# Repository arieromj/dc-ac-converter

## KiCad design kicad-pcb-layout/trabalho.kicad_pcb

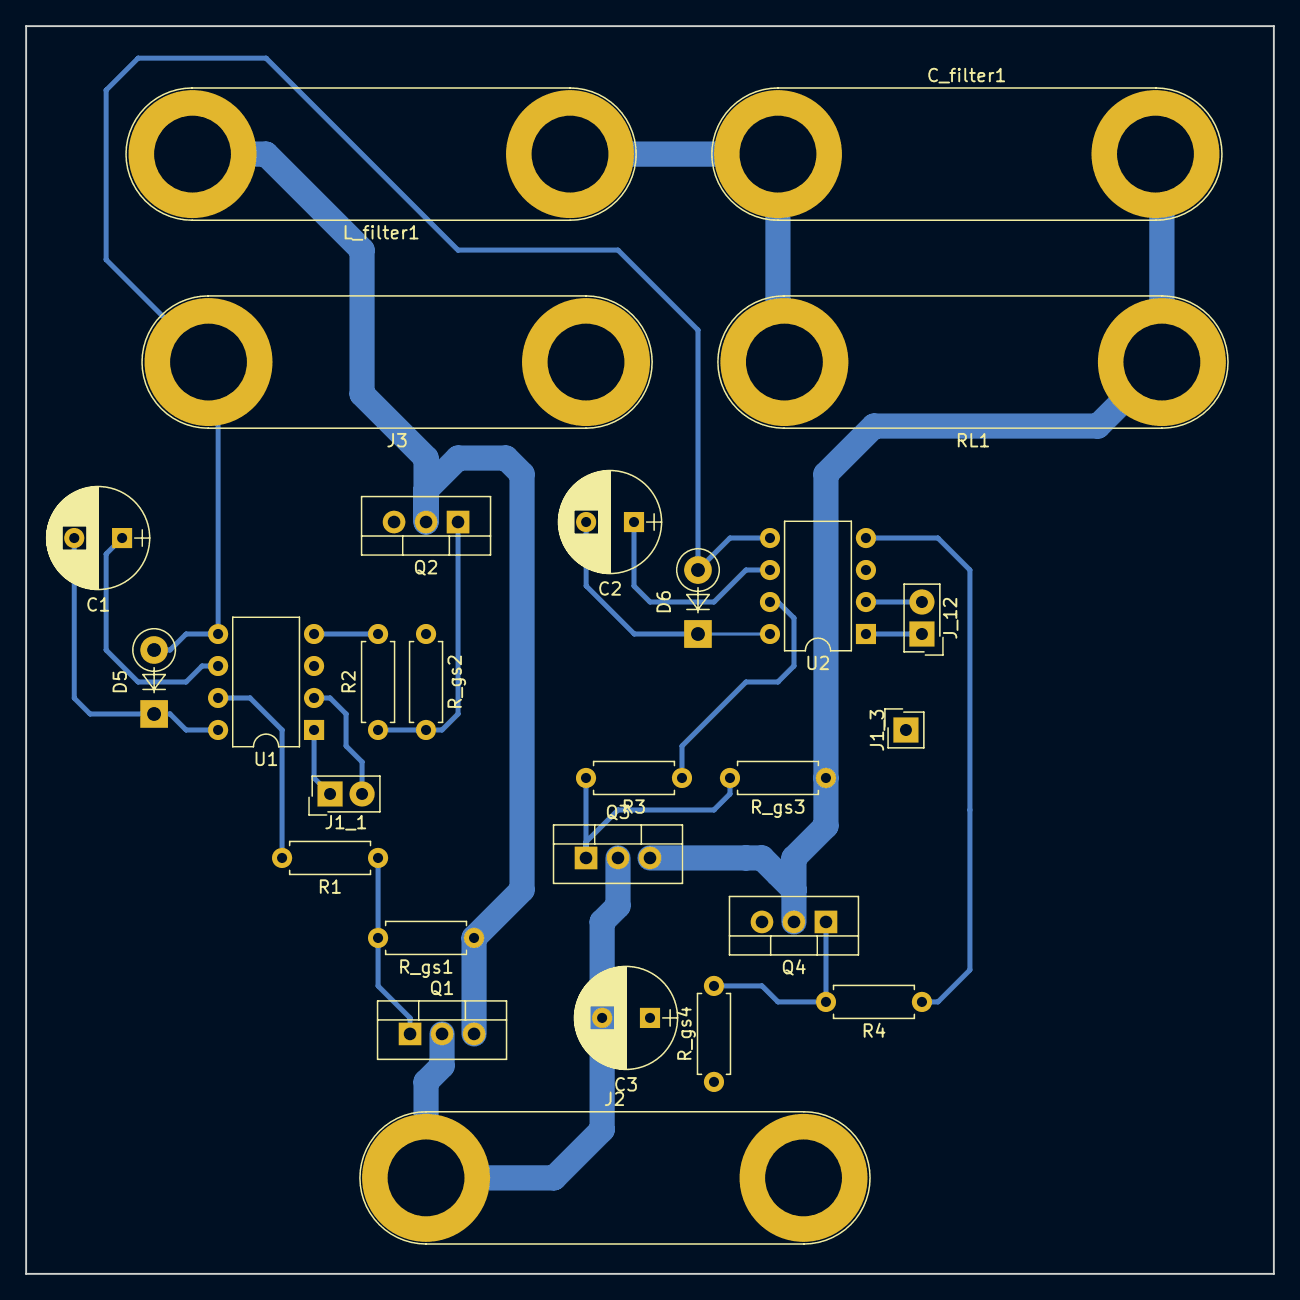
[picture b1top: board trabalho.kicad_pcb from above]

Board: 2 copper layers, 99.1 x 99.1 mm, 27 parts (0 on the bottom side), 22 nets.

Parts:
C1, C2, C3: C; CP_Radial_D8.0mm_P3.80mm
C_filter1: C; Banana_Jack_2Pin
D5, D6: 1N4007; D_DO-41_SOD81_P5.08mm_Vertical_KathodeUp
J1_1: CONN_01X02; SL-102-X-XX_1x02
J1_3: CONN_01X01; SL-101-X-XX_1x01
J2, J3: CONN_01X02; Banana_Jack_2Pin
J_12: CONN_01X02; SL-102-X-XX_1x02
L_filter1: L; Banana_Jack_2Pin
Q1, Q2, Q3, Q4: IRF540N; TO-220-3_Vertical
R1, R2, R3, R4: 150; R_Axial_DIN0207_L6.3mm_D2.5mm_P7.62mm_Horizontal
RL1: R; Banana_Jack_2Pin
R_gs1, R_gs2, R_gs3, R_gs4: 10k; R_Axial_DIN0207_L6.3mm_D2.5mm_P7.62mm_Horizontal
U1, U2: IRS2184; DIP-8_W7.62mm

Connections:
+15V: D5.2, D6.2, J3.2, U1.5, U2.5
/I/O_ARDUINO_PIN1_U1: J1_1.1, U1.1
/I/O_ARDUINO_PIN1_U2: J_12.1, U2.1
/I/O_ARDUINO_PIN2_U1: J1_1.2, U1.2
/I/O_ARDUINO_PIN2_U2: J_12.2, U2.2
/Vin: C3.2, J2.1, Q1.2, Q3.2
GNDREF: C3.1, J1_3.1, J2.2, J3.1, Q2.3, Q4.3, R_gs2.1, R_gs4.1, U1.3, U2.3
unnamed: C1.1, U1.6
unnamed: C1.2, D5.1, U1.8
unnamed: C2.1, U2.6
unnamed: C2.2, D6.1, U2.8
unnamed: C_filter1.1, L_filter1.1, RL1.2
unnamed: C_filter1.2, Q3.3, Q4.2, RL1.1, R_gs3.1
unnamed: L_filter1.2, Q1.3, Q2.2, R_gs1.1
unnamed: Q1.1, R1.1, R_gs1.2
unnamed: Q2.1, R2.1, R_gs2.2
unnamed: Q3.1, R3.2, R_gs3.2
unnamed: Q4.1, R4.2, R_gs4.2
unnamed: R1.2, U1.7
unnamed: R2.2, U1.4
unnamed: R3.1, U2.7
unnamed: R4.1, U2.4
